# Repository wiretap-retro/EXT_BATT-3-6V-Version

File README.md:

# EXT_BATT 3-6V Version
A battery supply for retro motherboards with an EXT_BATT header.

\

\
^--photo from minuszerodegrees showing EXT_BATT header

## Info
I have quite a few 386 and 486 motherboards that have an EXT_BATT header, but I've removed the rechargable Varta. This PCB project is aimed at using the EXT_BATT header to provide a solution to keep your CMOS settings saved and RTC ticking. The MAX40200 chip provides for "ideal diode" functionality with less than a 43mV drop in voltage. It also prevents a charge circuit from trying to charge the CR1220 type batteries if the motherboard happens to have a charge circuit on the EXT_BATT header. (rare occurences) I prefer this board because the batteries are cheap, last a long time, and the EXT_BATT header is usually in an easier spot to get to than where the Varta battery is crammed on most boards. Regardless, check the batteries every few years.

## BOM
* This circuit board, ordered from your fabricator of choice. (JLCPCB, PCBway, OSH Park, etc.)
* Maxim MAX40200AUK+T Ideal Diode
* 2x Keystone Electronics 2894 battery holders
* 1x04 2.54mm pitch right angle pin socket, or 1x04 2.54mm pitch straight pin socket, or 1x04 2.54mm male pin headers (see below for mounting orientations)
* (2) 1x02 2.54mm pitch straight pin headers
* (1) 1x02 2.54mm pitch jumper
* 1-2x CR1220 batteries

## Jumper Settings

|   J2  | J3    | Result |
| ---   | ---   | ---    |
| SHORT | OPEN  | 6V |
| OPEN  | SHORT | 3V |
| SHORT | SHORT | Smoke |
| OPEN  | OPEN  | Nothing |

For 3V, populate the rear battery only. For 6V, populate both batteries. The negative battery terminal faces the PCB.
\
\
3V may work for your board, as there are many people that report a single 3V lithium cell is able to power their RTC. Of course, it depends on the minimum input voltage rating for the RTC chip. For 6V, please check your motherboard manual first to see if it will accept a voltage at that level.

## Installation
Set the jumper and plug the completed board into the EXT_BATT header. Several motherboards also use an INTERNAL/EXTERNAL jumper to select between the factory installed battery and the EXT_BATT header.
\
\
Mounting orientations:
* Vertical - this PCB sits about 32mm tall when installed vertically. 
* Horizontal - may be possible depending on your board's EXT_BATT header location/orientation and other nearby components.
* Remote - use pin header extension wires to connect to the EXT_BATT header and put the PCB somewhere else in the case.

## Other
Reference material for retro motherboard batteries: http://minuszerodegrees.net/battery/cmos/vintage_motherboard_batteries.htm
\
This project is open source, feel free to do what you want with it.

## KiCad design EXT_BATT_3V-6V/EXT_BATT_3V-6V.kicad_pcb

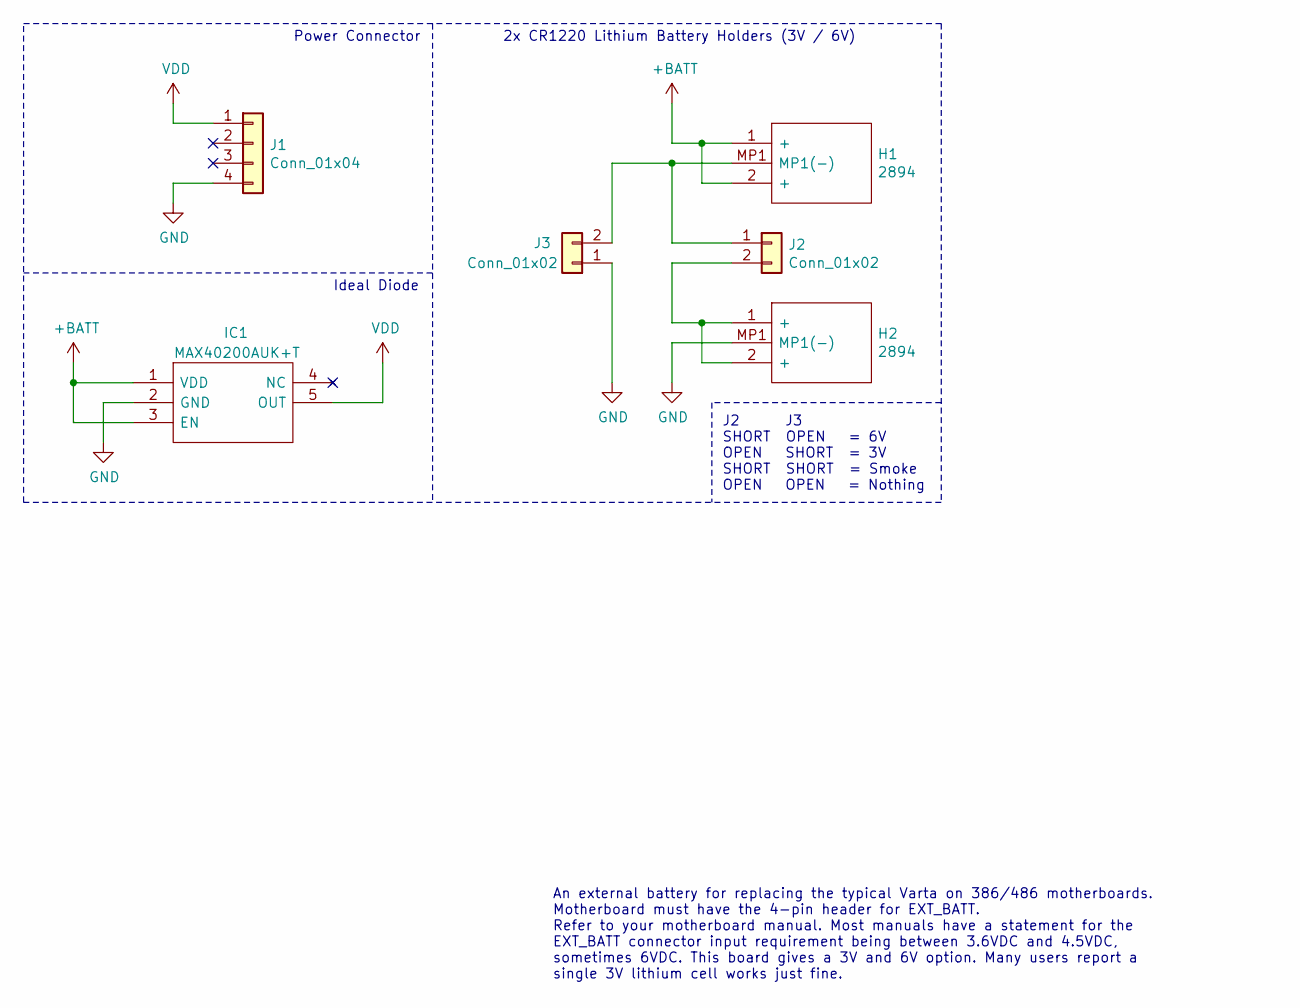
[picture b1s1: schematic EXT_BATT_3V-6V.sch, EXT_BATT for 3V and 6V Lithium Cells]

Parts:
H1, H2: 2894; Mouser Part Number 534-2894
IC1: MAX40200AUK+T; SOT95P280X145-5N; Mouser Part Number 700-MAX40200AUK+T
J1: Conn_01x04; PinSocket_1x04_P2.54mm_Horizontal
J2, J3: Conn_01x02; PinHeader_1x02_P2.54mm_Vertical

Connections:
+BATT: H1.1 (+), H1.2 (+), IC1.1 (VDD), IC1.3 (EN)
GND: H2.MP1 (MP1(-)), IC1.2 (GND), J1.4, J3.1
unnamed: H1.MP1 (MP1(-)), J2.1, J3.2
unnamed: H2.1 (+), H2.2 (+), J2.2
VDD: IC1.5 (OUT), J1.1

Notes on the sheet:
J2 J3 SHORT OPEN = 6V OPEN SHORT = 3V SHORT SHORT = Smoke OPEN OPEN = Nothing
Power Connector
Ideal Diode
2x CR1220 Lithium Battery Holders (3V / 6V)
An external battery for replacing the typical Varta on 386/486 motherboards. Motherboard must have the 4-pin header for EXT_BATT. Refer to your motherboard manual. Most manuals have a statement for the EXT_BATT connector input requirement being between 3.6VDC and 4.5VDC, sometimes 6VDC. This board 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

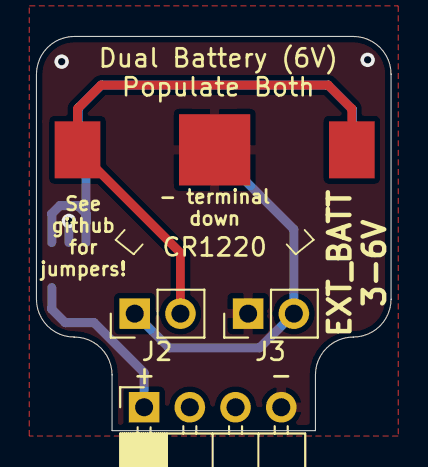
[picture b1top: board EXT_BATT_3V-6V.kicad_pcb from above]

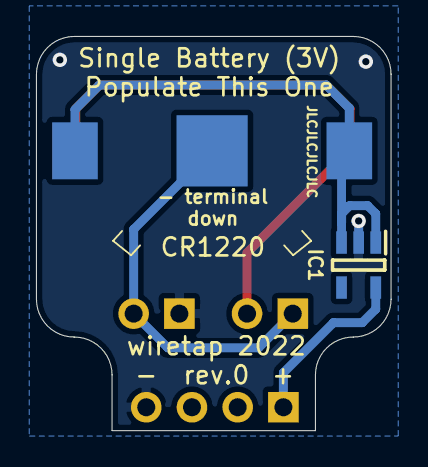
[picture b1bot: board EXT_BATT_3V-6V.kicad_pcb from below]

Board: 2 copper layers, 19.7 x 21.9 mm, 6 parts (2 on the bottom side), 5 nets.
